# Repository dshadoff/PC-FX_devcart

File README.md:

# PC-FX_devcart

This is a design of a development cart for the PC-FX, based almost entirely on the
RP2040 microcontroller.

##  Current Board Revision

The current version is Ver2_RevB.
[(For the Protoype board using an Olimex RP2040-Pico30 module, please click here.)](PC_board/README_prototype.md)

The only changes from RevA to Rev B are related to schematic annotations, and a minor labelling update on the PC
Board itself, so the picture of RevA is included here.

In future, there are plans for a proper 3D printed case.

## Genesis of the Project

The basis of the FX-BMP cartridge is that it consists of 128KB of memory, and the PC-FX can
actually boot from the cartridge memory under the right circumstances.

The FX-BMP memory doesn't need to be very fast - the bus access speed is cut in half when
accessing the FX-BMP range of memory. Assuming that the CPU reads the data at the rising
edge of /OE, this can be as slow as 174ns after /OE. (My design targets have been to keep this
turnaround time below 150ns).

The RP2040 has two CPU cores, and very fast GPIO access. It seemed possible to emply one
CPU core to deal with external access to the memory - emulating a SRAM bus interface - and
for the other CPU core to be used as a supervisor, allowing USB commands to read/write this
memory, downloading programs and preparing them to be booted from.

## Theory of Operation

### Signal Timing - Read

At 21MHz, you would expect the PC-FX to have a very fast bus access speed, however accesses to
the FX-BMP port are apparently clocked at half-speed (and are only 8 bits wide).

In general, bus accesses progress through the following steps for a read cycle:
- Address lines are set up
- /CE transitions low
- /OE transitions low
- The device being queried needs to ready the data, and output it onto the data bus
- /OE transitions high
- The device being queried needs to de-assert/tri-state its outputs
- /CE transitions high

While this is the normal situation, there can also be cases where the /CE line does not return to
high state before a subsequent address setup and corresponding /OE (or /WE) transition to low.

As our circuit operates at 3.3V, keep in mind that good-quality level-shifters will delay incoming
signals by roughly 5ns before they appear, and an additional 10ns on the return path, reducing the
available turnaround time for a read transaction.

Here is a visual of the actual timing of those sequences:

### Signal Timing - Write

In general, bus accesses progress through the following steps for a write cycle:
- Address lines are set up
- /CE transitions low
- /WE transitions low
- Data appears on the bus, to be written to the addressed device (not before /WE !)
- /WE transitions high
- In theory, the written-to device should latch data at this monment, but we can't react that fast, so we will latch earlier
- /CE transitions high

While this is the normal situation, there can also be cases where the /CE line does not returns to
high state before a subsequent address setup and corresponding /WE (or /OE) transition to low.

Here is a visual of the actual timing of those sequences:

### GPIO Versus PIO

My original idea was to emply PIOs to manage the bus, but there are delays in crossing
between CPU and PIO (to access the CPU's memory), which hobbled performance.  However,
it turned out that the GPIO access functions are also very fast, enabling the RP2040 to
reach the apparent required speed.

### CPU Overclock

In order the reach the required speeds, the CPU is overclocked to 240MHz (the default
CPU clock speed is only 125MHz, and it is only certified to 133MHz). This might at first
sound a bit scary and possibly dangerous, but there are many cases of RP2040 examples out
in the wild and used commonly which are clocked over 250MHz (including dricing VGA and
DVI/HDMI signals), with many people finding it to work in the 400MHz range (of course,
USB and Flash access break down somewhere between 250MHz and 400MHz).

### GPIOs in USE

| GPIO | Signal |
|------|--------|
| GPIO0 | D0 |
| GPIO1 | D1 |
| GPIO2 | D2 |
| GPIO3 | D3 |
| GPIO4 | D4 |
| GPIO5 | D5 |
| GPIO6 | D6 |
| GPIO7 | D7 |
| GPIO8 | A0 |
| GPIO9 | A1 |
| GPIO10 | A2 |
| GPIO11 | A3 |
| GPIO12 | A4 |
| GPIO13 | A5 |
| GPIO14 | A6 |
| GPIO15 | A7 |
| GPIO16 | A8 |
| GPIO17 | A9 |
| GPIO18 | A10 |
| GPIO19 | A11 |
| GPIO20 | A12 |
| GPIO21 | A13 |
| GPIO22 | A14 |
| GPIO23 | A15 |
| GPIO24 | A16 |
| GPIO25 | A17 |
| GPIO26 | /CE |
| GPIO27 | /OE |
| GPIO28 | /WE |

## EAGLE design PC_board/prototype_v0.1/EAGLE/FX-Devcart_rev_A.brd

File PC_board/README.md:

# PC-FX_devcart PC Board

This is the PC board design of a development cart for the PC-FX, based on the RP2040 microcontroller.

##  Current version

The current version is Ver2_RevB.
[(For the Protoype board using an Olimex RP2040-Pico30 module, please click here.)](README_prototype.md)

The only changes from RevA to Rev B are related to schematic annotations, and a minor labelling update on the PC Board itself,
so the picture of RevA is included here.

## Overview

The board design was a ground-up design for 4-layer board using KiCAD 8.0.4 .

As this was my first KiCAD design of a reasonable complexity, I was happy to receive some guidance
and schematic updates from [Regis Galland](https://github.com/rgalland).

The board is based around a RP2040 microcontroller, and its "minimal design", as shown in the Raspberry Pi
[Hardware Design With RP2040 Design Guide](https://datasheets.raspberrypi.com/rp2040/hardware-design-with-rp2040.pdf).

The bus decoding was based on my earlier work with the [PC-FX_nvBMP board](https://github.com/pcfx-devel/PC-FX-NVBMP).

The 3.3V power is not derived from PC-FX's power: The RP2040 is powered from the USB host, and an on-board
3.3V regulator provides the 3.3V rail for the module and the 3.3V side of the level-shifters.

Only the 5V side of the level-shifters is supplied by the PC-FX (however, they share a common ground).

This means that:
 1) The FX-devcart board will not function correctly when not connected to USB, as this is the main power source.
 2) The FX-devcart can be programmed while inserted into the PC-FX, while the PC-FX is not turned on - this is
important for the ability to "boot" code from teh FX-devcart

## Files

KiCAD was used for designing the board, and all design files are included.
(FX-Dev_Ver2_revB.zip is a KiCAD Project archive, including all relevant footprints and datasheets).

In order to manufacture the board, the key files are in the "production" subfolder:
 - Gerber files are supplied in the relevant 'Gerbersi_xxx.zip' file.
 - bom.csv is the bill-of-materials file, prepared in the format for JLCPCB's assembly service
 - positions.csv is the pick-and-place part positioning file, prepared in the format for JLCPCB's assembly service

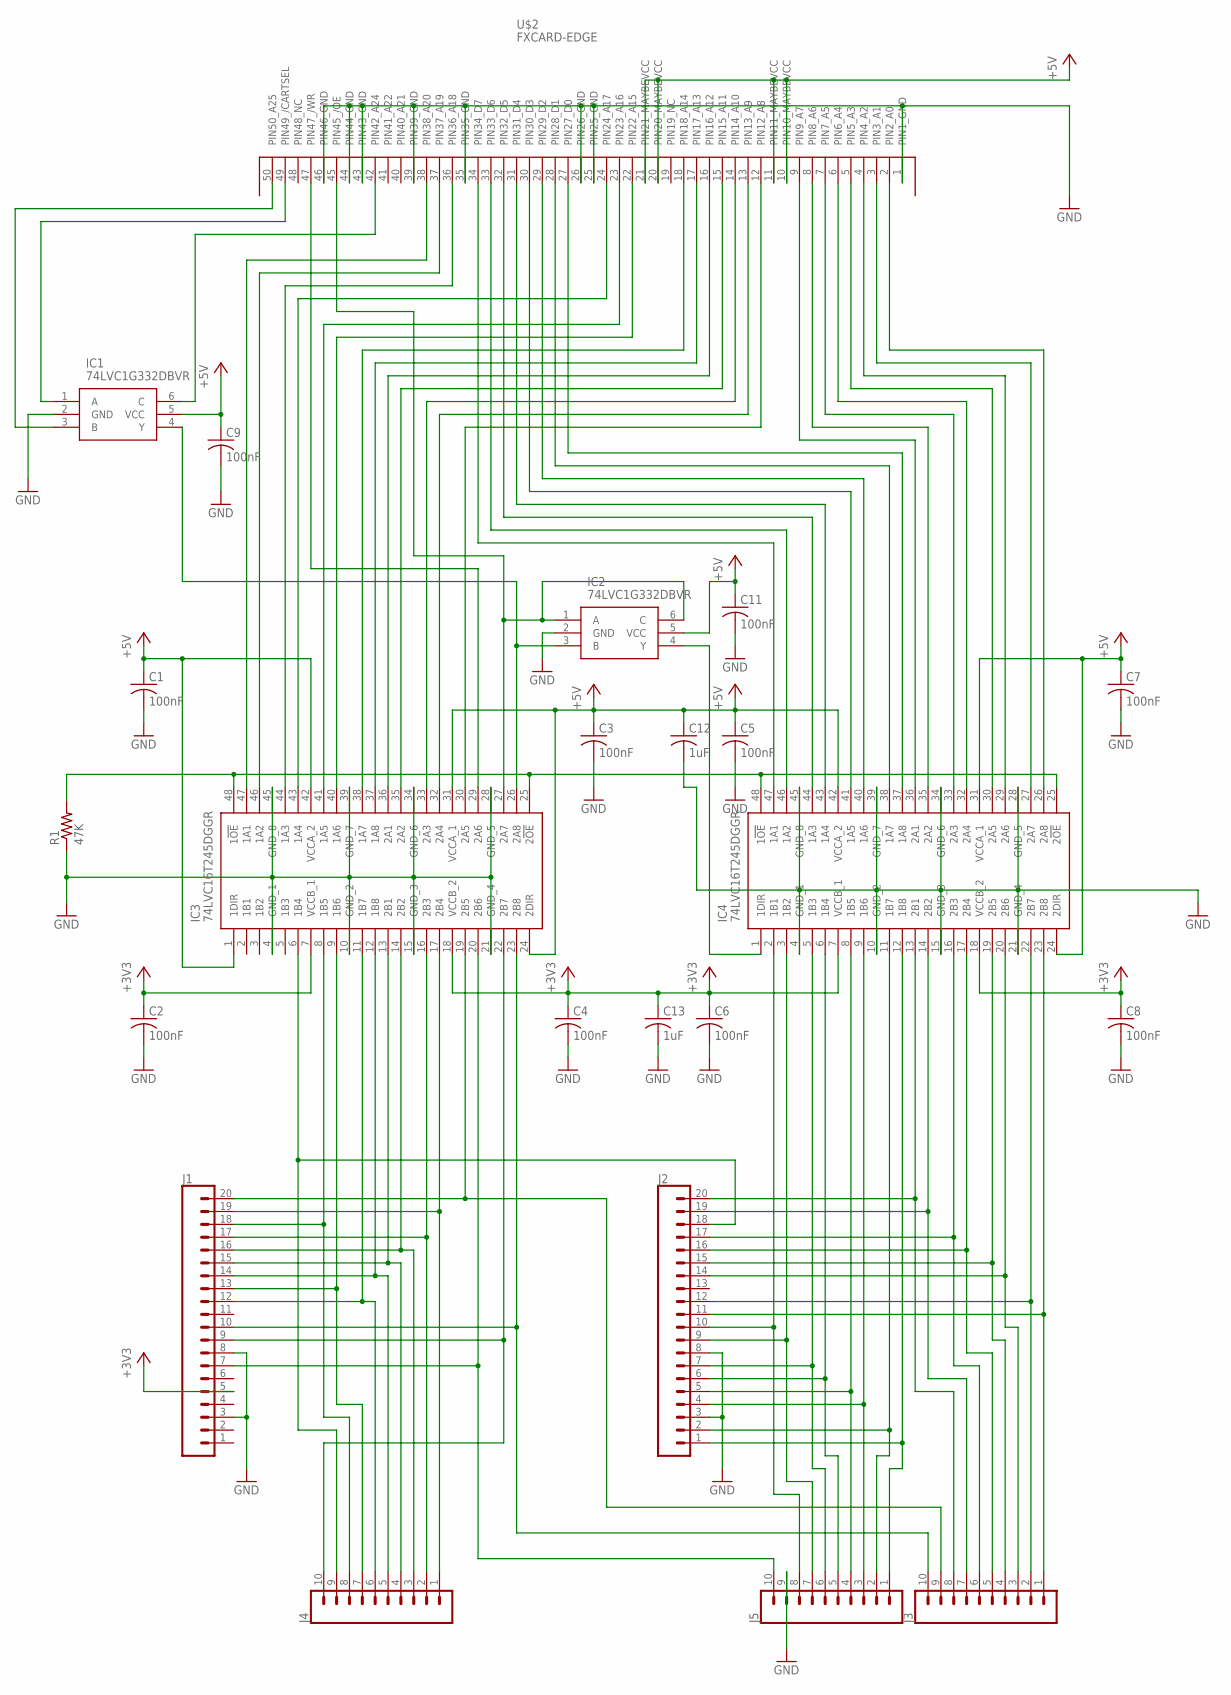
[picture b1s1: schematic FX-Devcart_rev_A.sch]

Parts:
C1, C2, C3, C4, C5, C6, C7, C8, C9, C11: 100nF; C0402
C12, C13: 1uF; C0402
IC1, IC2: 74LVC1G332DBVR; SOT95P280X145-6N
IC3, IC4: 74LVC16T245DGGR; SOP50P810X120-48N
J1, J2: CONN_20NOSILK; 1X20_NOSILK
J3, J4, J5: CONN_10NO_SILK_PTH_FEMALE; 1X10_NO_SILK
R1: 47K; R0402
U$2: FXCARD-EDGE

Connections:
+3V3: C2.1, C4.1, C6.1, C8.1, C13.1, IC3.7 (VCCB_1), IC3.18 (VCCB_2), IC4.7 (VCCB_1), IC4.18 (VCCB_2), J1.5
+5V: C1.1, C3.1, C5.1, C7.1, C9.1, C11.1, C12.1, IC1.5 (VCC), IC2.5 (VCC), IC3.1 (1DIR), IC3.24 (2DIR), IC3.31 (VCCA_1), IC3.42 (VCCA_2), IC4.24 (2DIR), IC4.31 (VCCA_1), IC4.42 (VCCA_2), U$2.10 (PIN10_MAYBEVCC), U$2.11 (PIN11_MAYBEVCC), U$2.20 (PIN20_MAYBEVCC), U$2.21 (PIN21_MAYBEVCC)
GND: C1.2, C2.2, C3.2, C4.2, C5.2, C6.2, C7.2, C8.2, C9.2, C11.2, C12.2, C13.2, IC1.2 (GND), IC2.2 (GND), IC3.4 (GND_1), IC3.10 (GND_2), IC3.15 (GND_3), IC3.21 (GND_4), IC3.28 (GND_5), IC3.34 (GND_6), IC3.39 (GND_7), IC3.45 (GND_8), IC4.4 (GND_1), IC4.10 (GND_2), IC4.15 (GND_3), IC4.21 (GND_4), IC4.28 (GND_5), IC4.34 (GND_6), IC4.39 (GND_7), IC4.45 (GND_8), J1.3, J1.8, J2.3, J2.8, J5.9, R1.1, U$2.1 (PIN1_GND), U$2.25 (PIN25_GND), U$2.26 (PIN26_GND), U$2.35 (PIN35_GND), U$2.39 (PIN39_GND), U$2.43 (PIN43_GND), U$2.44 (PIN44_GND), U$2.46 (PIN46_GND)
unnamed: IC4.37 (1A8), U$2.27 (PIN27_D0)
unnamed: IC4.38 (1A7), U$2.28 (PIN28_D1)
unnamed: IC4.40 (1A6), U$2.29 (PIN29_D2)
unnamed: IC4.41 (1A5), U$2.30 (PIN30_D3)
unnamed: IC4.43 (1A4), U$2.31 (PIN31_D4)
unnamed: IC4.44 (1A3), U$2.32 (PIN32_D5)
unnamed: IC4.46 (1A2), U$2.33 (PIN33_D6)
unnamed: IC4.47 (1A1), U$2.34 (PIN34_D7)
unnamed: IC4.26 (2A8), U$2.2 (PIN2_A0)
unnamed: IC4.27 (2A7), U$2.3 (PIN3_A1)
unnamed: IC4.29 (2A6), U$2.4 (PIN4_A2)
unnamed: IC4.30 (2A5), U$2.5 (PIN5_A3)
unnamed: IC4.33 (2A3), U$2.7 (PIN7_A5)
unnamed: IC3.43 (1A4), U$2.24 (PIN24_A17)
unnamed: IC4.35 (2A2), U$2.8 (PIN8_A6)
unnamed: IC4.36 (2A1), U$2.9 (PIN9_A7)
unnamed: IC4.32 (2A4), U$2.6 (PIN6_A4)
unnamed: IC3.44 (1A3), U$2.36 (PIN36_A18)
unnamed: IC3.46 (1A2), U$2.37 (PIN37_A19)
unnamed: IC3.47 (1A1), U$2.38 (PIN38_A20)
unnamed: IC1.4 (Y), IC2.3 (B), IC3.26 (2A8)
unnamed: IC3.25 (2!OE), IC3.48 (1!OE), IC4.25 (2!OE), IC4.48 (1!OE), R1.2
unnamed: IC4.23 (2B8), J2.11, J3.1
unnamed: IC4.22 (2B7), J2.12, J3.2
unnamed: IC4.20 (2B6), J2.14, J3.3
unnamed: IC2.4 (Y), IC4.1 (1DIR)
unnamed: IC4.19 (2B5), J2.15, J3.4
unnamed: IC4.17 (2B4), J2.16, J3.5
unnamed: IC4.16 (2B3), J2.17, J3.6
unnamed: IC4.14 (2B2), J2.19, J3.7
unnamed: IC4.13 (2B1), J2.20, J3.8
unnamed: IC4.12 (1B8), J2.1, J5.1
unnamed: IC3.30 (2A5), U$2.12 (PIN12_A8)
unnamed: IC3.32 (2A4), U$2.13 (PIN13_A9)
unnamed: IC3.33 (2A3), U$2.14 (PIN14_A10)
unnamed: IC3.35 (2A2), U$2.15 (PIN15_A11)
unnamed: IC3.36 (2A1), U$2.16 (PIN16_A12)
unnamed: IC3.37 (1A8), U$2.17 (PIN17_A13)
unnamed: IC3.38 (1A7), U$2.18 (PIN18_A14)
unnamed: IC3.40 (1A6), U$2.22 (PIN22_A15)
unnamed: IC3.41 (1A5), U$2.23 (PIN23_A16)
unnamed: IC3.29 (2A6), U$2.47 (PIN47_/WR)
unnamed: IC2.1 (A), IC2.6 (C), IC3.27 (2A7), U$2.45 (PIN45_/OE)
unnamed: IC1.3 (B), U$2.50 (PIN50_A25)
unnamed: IC1.1 (A), U$2.49 (PIN49_/CARTSEL)
unnamed: IC1.6 (C), U$2.42 (PIN42_A24)
unnamed: IC4.11 (1B7), J2.2, J5.2
unnamed: IC4.9 (1B6), J2.4, J5.3
unnamed: IC4.8 (1B5), J2.5, J5.4
unnamed: IC4.6 (1B4), J2.6, J5.5
unnamed: IC4.5 (1B3), J2.7, J5.6
unnamed: IC4.3 (1B2), J2.9, J5.7
unnamed: IC3.20 (2B6), J1.7, J5.10
unnamed: IC3.19 (2B5), J1.20, J3.9
unnamed: IC3.17 (2B4), J1.19, J4.1
unnamed: IC3.16 (2B3), J1.17, J4.2
unnamed: IC3.14 (2B2), J1.16, J4.3
unnamed: IC3.13 (2B1), J1.15, J4.4
unnamed: IC3.12 (1B8), J1.14, J4.5
unnamed: IC3.11 (1B7), J1.12, J4.6
unnamed: IC3.9 (1B6), J1.13, J4.7
unnamed: IC3.8 (1B5), J1.18, J4.8
unnamed: IC3.6 (1B4), J2.18, J4.9
unnamed: IC3.22 (2B7), J1.9, J4.10
unnamed: IC3.23 (2B8), J1.10, J3.10
unnamed: IC4.2 (1B1), J2.10, J5.8

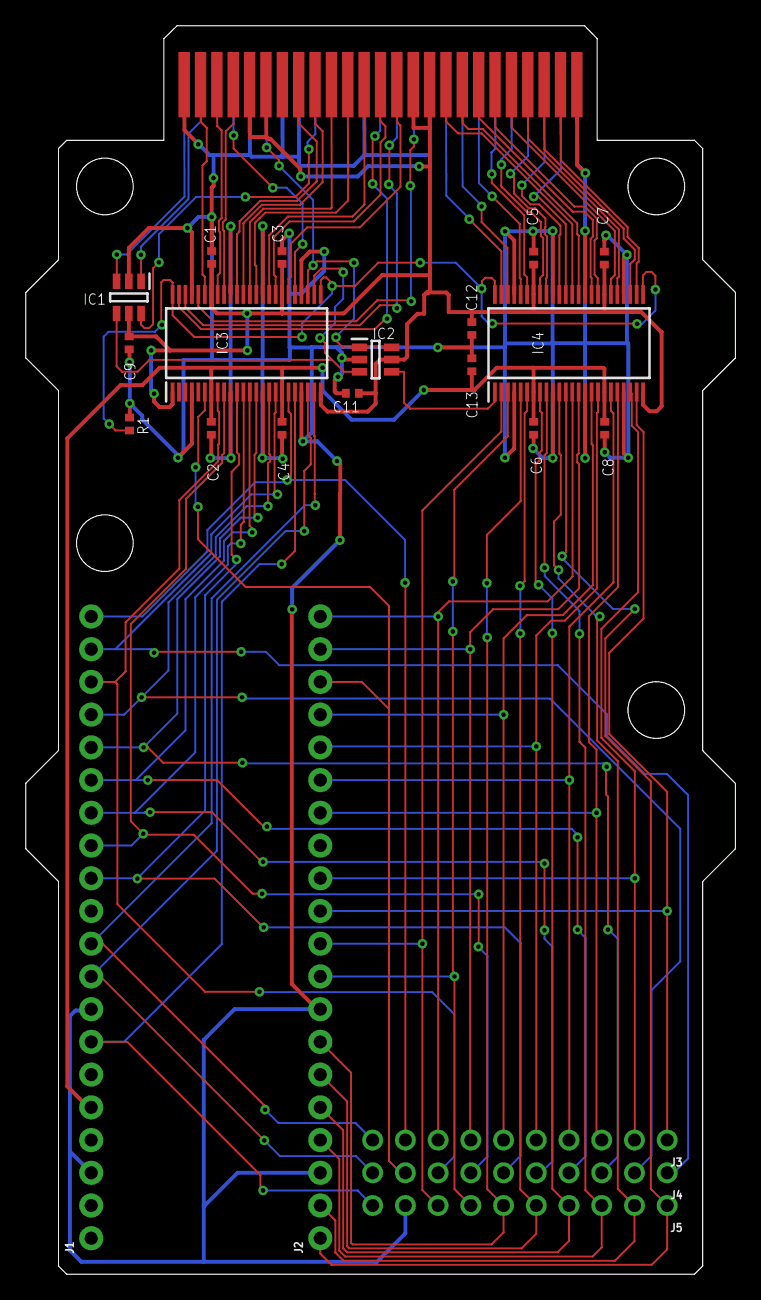
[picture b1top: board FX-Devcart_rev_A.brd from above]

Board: 2 copper layers, 55.1 x 96.9 mm, 23 parts (0 on the bottom side), 69 nets.

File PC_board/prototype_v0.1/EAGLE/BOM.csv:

Qty,Designator,Footprint,Comment,LCSC Part # (optional),Description (optional)
10,"C1, C2, C3, C4, C5, C6, C7, C8, C9, C11",C0402,100nF 16V,C1525,Samsung CL05B104KO5NNNC 100nF 16V 0402
2,"C12, C13",C0402,1uF 25V,C52923,Samsung CL05A105KA5NQNC 1uF 25V 0402
1,R1,R0402,47K,C25741,62.5mW Thick Film Resistors 50V ±100ppm/_ ±1% -55_~+155_ 100kΩ 0402 Chip Resistor - Surface Mount ROHS
2,"IC3, IC4",TSSOP-48,74LVC16T245DGGR,C148170,"Texas Instruments 74LVC16T245DGGR, Dual, Bus Transceiver, 16-Bit Non-Inverting LVTTL, 1.65  5.5 V, 48-Pin TSSOP"
2,"IC1, IC2",SOT-23-6,74LVC1G332DBVR,C43368,"Texas Instruments 74LVC1G332DBVR, 3-Input OR Logic Gate, 1.65  5.5 V, 6-Pin SOT-23"

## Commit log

2024-03-07 Initial commit of PC-side commands
2024-03-07 Updates to the program running on the devcart
2024-03-08 Minor update & rough-in timing/speed check
2024-03-09 Add circuit board design
2024-03-09 Get FIFO working (on cart) and clean up code a bit
2024-03-09 Add PC side Python script for reading FIFO port output from PCFX
2024-03-09 Add some basic information about how to use the FIFO port in your PCFX project
2024-03-09 Some initial documents
2024-03-09 Update timing
2024-03-10 More documentation
2024-03-17 Update to create bootloader to allow programs larger than 128KB to be loaded
2024-05-12 Documentation updates
2024-10-02 Improve speed, allow compile on SDK 2.0.0
2024-10-02 Fix access for FIFO port addresses; allow compile on SDK2.0.0
2024-10-16 More (minor) updates to firmware
2024-10-16 more minor updates
2024-10-20 Update PC Board files for new version
2024-10-20 Fixes to text and image
2024-10-20 fixes, typos
2024-10-20 typos
2024-11-10 Update position of USB-C connector, and add STEP file
2024-11-11 Fix some internal referecnes & correct STEP file
2024-11-18 Add enclosure (currently in prototype/validation stage)
2024-11-28 Minor adjustment to screw hole radii

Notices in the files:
PC_board/prototype_v0.1/EAGLE/FX-Devcart_rev_A.brd:
(c) 2024
parts and their libraries:
SparkFun-Connectors: Licensing: Creative Commons ShareAlike 4.0 International - https://creativecommons.org/licenses/by-sa/4.0
